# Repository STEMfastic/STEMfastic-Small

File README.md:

# STEMfastic-Small
A small Atmel ATMEGA328P project.

http://www.stemfastic.co.uk/

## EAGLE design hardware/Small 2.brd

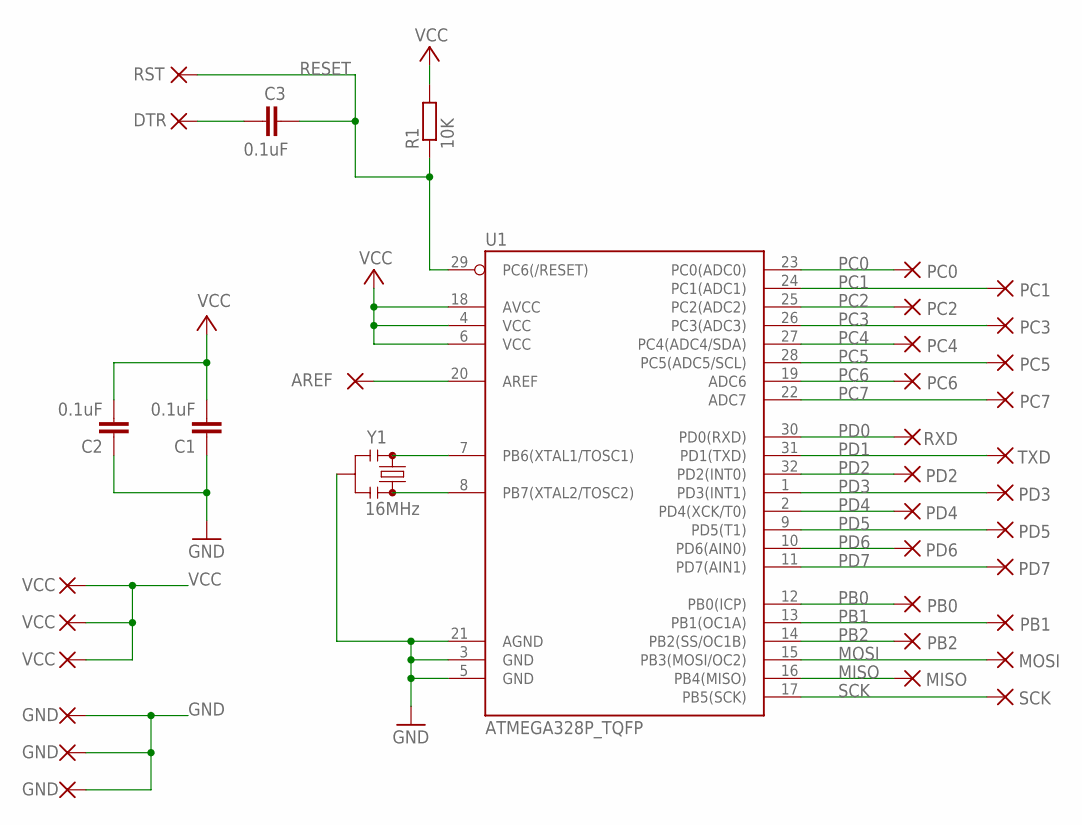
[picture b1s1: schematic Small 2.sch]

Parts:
AREF: 1,6/0,8
C1, C2, C3: 0.1uF; C0603
DTR: 1,6/0,8
DTR1: RST; 1,6/0,8
GND, GND3, GND4: GND; 1,6/0,8
MISO: MISO; 1,6/0,8
MOSI: MOSI; 1,6/0,8
PB0, PB1, PB2: 1,6/0,8
PC0, PC1, PC2, PC3, PC4, PC5, PC6, PC7: 1,6/0,8
PD2, PD3, PD4, PD5, PD6, PD7: 1,6/0,8
R1: 10K; R0603
RXD: 1,6/0,8
SCK: SCK; 1,6/0,8
TXD: 1,6/0,8
U1: ATMEGA328P_TQFP; TQFP32-08
VCC, VCC1, VCC2: VCC; 1,6/0,8
Y1: 16MHz; RESONATOR-SMD-3.2X1.3

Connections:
GND: C1.1, C2.1, GND.1, GND3.1, GND4.1, U1.3 (GND), U1.5 (GND), U1.21 (AGND), Y1.2
MISO: MISO.1, U1.16 (PB4(MISO))
MOSI: MOSI.1, U1.15 (PB3(MOSI/OC2))
unnamed: C3.1, DTR.1
unnamed: U1.7 (PB6(XTAL1/TOSC1)), Y1.1
unnamed: U1.8 (PB7(XTAL2/TOSC2)), Y1.3
unnamed: AREF.1, U1.20 (AREF)
PB0: PB0.1, U1.12 (PB0(ICP))
PB1: PB1.1, U1.13 (PB1(OC1A))
PB2: PB2.1, U1.14 (PB2(SS/OC1B))
PC0: PC0.1, U1.23 (PC0(ADC0))
PC1: PC1.1, U1.24 (PC1(ADC1))
PC2: PC2.1, U1.25 (PC2(ADC2))
PC3: PC3.1, U1.26 (PC3(ADC3))
PC4: PC4.1, U1.27 (PC4(ADC4/SDA))
PC5: PC5.1, U1.28 (PC5(ADC5/SCL))
PC6: PC6.1, U1.19 (ADC6)
PC7: PC7.1, U1.22 (ADC7)
PD0: RXD.1, U1.30 (PD0(RXD))
PD1: TXD.1, U1.31 (PD1(TXD))
PD2: PD2.1, U1.32 (PD2(INT0))
PD3: PD3.1, U1.1 (PD3(INT1))
PD4: PD4.1, U1.2 (PD4(XCK/T0))
PD5: PD5.1, U1.9 (PD5(T1))
PD6: PD6.1, U1.10 (PD6(AIN0))
PD7: PD7.1, U1.11 (PD7(AIN1))
RESET: C3.2, DTR1.1, R1.1, U1.29 (PC6(/RESET))
SCK: SCK.1, U1.17 (PB5(SCK))
VCC: C1.2, C2.2, R1.2, U1.4 (VCC), U1.6 (VCC), U1.18 (AVCC), VCC.1, VCC1.1, VCC2.1

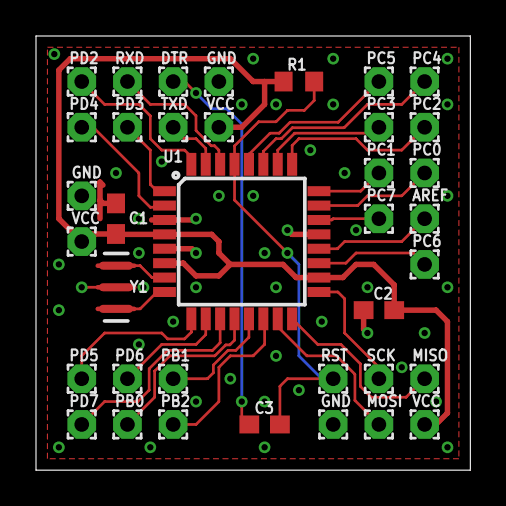
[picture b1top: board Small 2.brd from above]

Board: 2 copper layers, 24.1 x 24.1 mm, 37 parts (0 on the bottom side), 29 nets.

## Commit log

2020-01-06 Rename Small 2.sch to hardware/Small 2.sch

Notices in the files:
parts and their libraries:
SparkFun-IC-Microcontroller: Licensing: Creative Commons ShareAlike 4.0 International - https://creativecommons.org/licenses/by-sa/4.0
